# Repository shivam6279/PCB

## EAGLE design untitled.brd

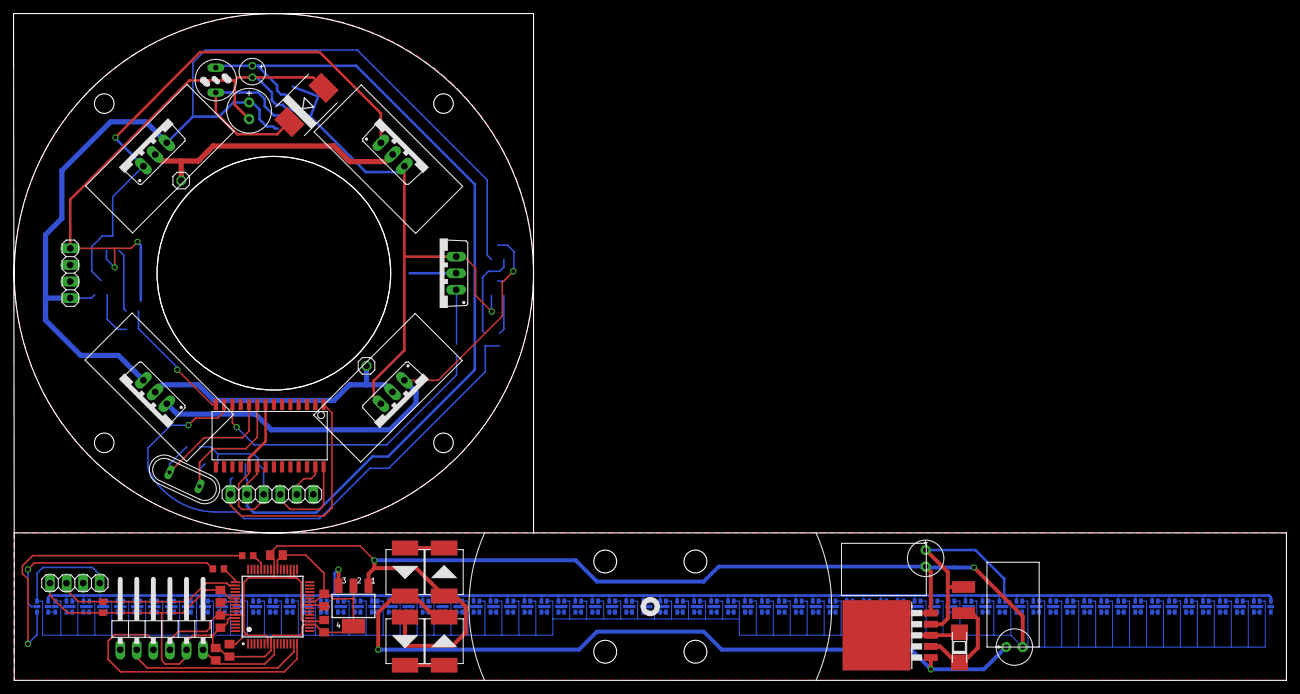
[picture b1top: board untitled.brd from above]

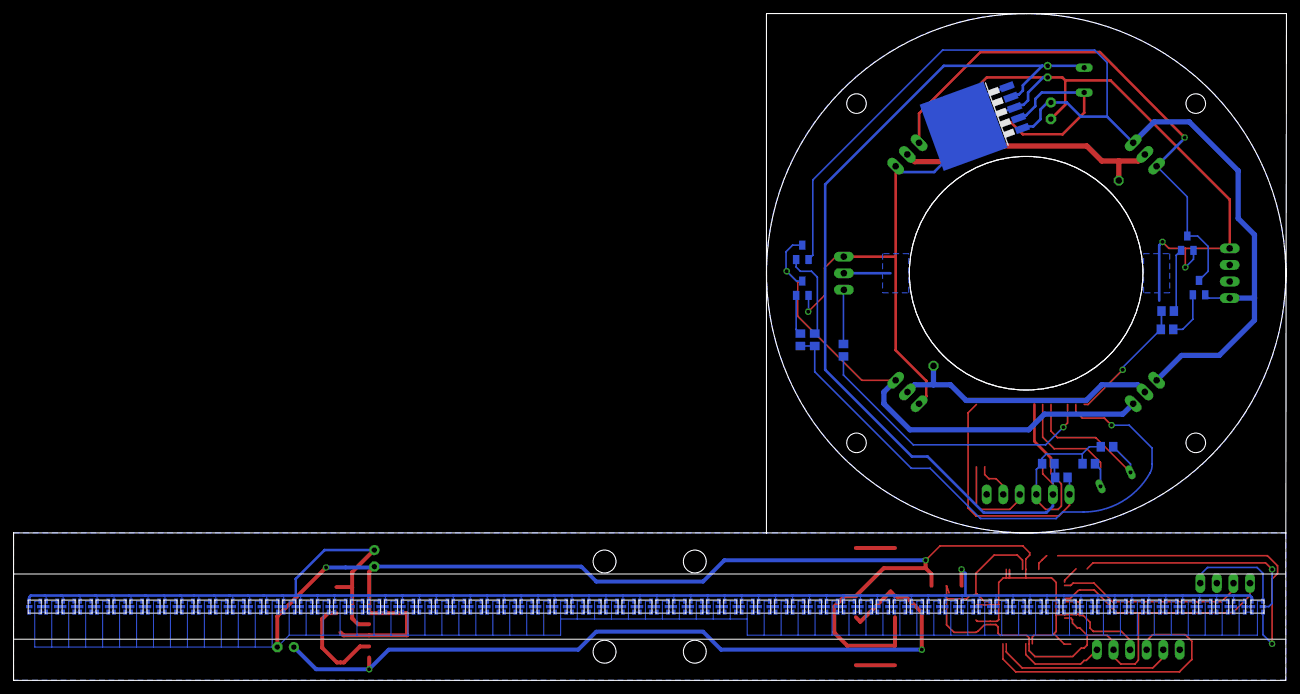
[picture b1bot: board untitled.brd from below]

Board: 2 copper layers, 195.1 x 102.2 mm, 125 parts (87 on the bottom side), 180 nets.

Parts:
C1, C3: E2,5-6E
C2, C4, C5, C6, C7, C8, C9, C10, C11: C0805
C12: E2,5-7
C13: E1,8-4
D1: SOD106A
D2, D3, D4, D5: SMD-DIODE-SCHOTTKY-40V-3A(DO-214AB); DO-214AB
D6: DIODE_SMC
IC1, IC4: LM2576S; TO263-5
IC2: SOT223
IC3: PIC16F876SO; SO28W
JP1: 1X06/90
JP2, JP3: 1X04
JP4: 1X06
JP5, JP6: 1X01
L1: 82114R
L2: L4532P
Q1, Q2, Q3, Q4: SOT23
Q5, Q6: IRF540; TO220BV
Q7, Q9: TO220BV
Q8: QS
R1, R3, R6, R7, R8, R9, R10: R0805
R2, R4, R5: R0603
T2: 2SC1306; TO220BV
U1: PIC32MZ2048EFH064-I/PT; QFP50P1200X1200X120-64N
U$1, U$2, U$3, U$4, U$5, U$6, U$7, U$8, U$9, U$10, U$11, U$12, U$13, U$14, U$15, U$16, U$17, U$18, U$19, U$20, U$21, U$22, U$23, U$24, U$25, U$26, U$27, U$28, U$29, U$30, U$31, U$32, U$33, U$34, U$35, U$36, U$37, U$38, U$39, U$40, U$41, U$42, U$43, U$44, U$45, U$46, U$47, U$48, U$49, U$50, U$51, U$52, U$53, U$54, U$55, U$56, U$57, U$58, U$59, U$60, U$61, U$62, U$63, U$64, U$65, U$66, U$67, U$68, U$69, U$70, U$71, U$72, U$73: 2020LED

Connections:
+3V3: C2.1, C4.1, C5.1, C6.1, C7.1, C8.1, IC2.2, JP1.5, JP2.1, R1.1, R2.1, U1.8, U1.19, U1.26, U1.39, U1.54, U1.60
+5V: C1.+, IC1.4, IC2.3, L2.2, U$1.VCC, U$2.VCC, U$3.VCC, U$4.VCC, U$5.VCC, U$6.VCC, U$7.VCC, U$8.VCC, U$9.VCC, U$10.VCC, U$11.VCC, U$12.VCC, U$13.VCC, U$14.VCC, U$15.VCC, U$16.VCC, U$17.VCC, U$18.VCC, U$19.VCC, U$20.VCC, U$21.VCC, U$22.VCC, U$23.VCC, U$24.VCC, U$25.VCC, U$26.VCC, U$27.VCC, U$28.VCC, U$29.VCC, U$30.VCC, U$31.VCC, U$32.VCC, U$33.VCC, U$34.VCC, U$35.VCC, U$36.VCC, U$37.VCC, U$38.VCC, U$39.VCC, U$40.VCC, U$41.VCC, U$42.VCC, U$43.VCC, U$44.VCC, U$45.VCC, U$46.VCC, U$47.VCC, U$48.VCC, U$49.VCC, U$50.VCC, U$51.VCC, U$52.VCC, U$53.VCC, U$54.VCC, U$55.VCC, U$56.VCC, U$57.VCC, U$58.VCC, U$59.VCC, U$60.VCC, U$61.VCC, U$62.VCC, U$63.VCC, U$64.VCC, U$65.VCC, U$66.VCC, U$67.VCC, U$68.VCC, U$69.VCC, U$70.VCC, U$71.VCC, U$72.VCC, U$73.VCC
+5V1: C9.2, C13.+, IC3.20, IC4.4, JP4.2, L1.2, R9.2
+12V: C12.+, IC4.1, JP3.1, Q3.2, Q4.2, Q7.S, Q9.S
+15V: C3.+, D2.2, D3.2, IC1.1
GND: C1.-, C2.2, C3.-, C4.2, C5.2, C6.2, C7.2, C8.2, D1.A, D4.1, D5.1, IC1.3, IC1.5, IC2.1, JP1.4, JP2.4, U1.7, U1.20, U1.25, U1.34, U1.35, U1.40, U1.55, U1.59, U$1.GND, U$2.GND, U$3.GND, U$4.GND, U$5.GND, U$6.GND, U$7.GND, U$8.GND, U$9.GND, U$10.GND, U$11.GND, U$12.GND, U$13.GND, U$14.GND, U$15.GND, U$16.GND, U$17.GND, U$18.GND, U$19.GND, U$20.GND, U$21.GND, U$22.GND, U$23.GND, U$24.GND, U$25.GND, U$26.GND, U$27.GND, U$28.GND, U$29.GND, U$30.GND, U$31.GND, U$32.GND, U$33.GND, U$34.GND, U$35.GND, U$36.GND, U$37.GND, U$38.GND, U$39.GND, U$40.GND, U$41.GND, U$42.GND, U$43.GND, U$44.GND, U$45.GND, U$46.GND, U$47.GND, U$48.GND, U$49.GND, U$50.GND, U$51.GND, U$52.GND, U$53.GND, U$54.GND, U$55.GND, U$56.GND, U$57.GND, U$58.GND, U$59.GND, U$60.GND, U$61.GND, U$62.GND, U$63.GND, U$64.GND, U$65.GND, U$66.GND, U$67.GND, U$68.GND, U$69.GND, U$70.GND, U$71.GND, U$72.GND, U$73.GND
GND1: C9.1, C10.1, C11.1, C12.-, C13.-, D6.A, IC3.8, IC3.19, IC4.3, IC4.5, JP3.4, JP4.3, Q1.2, Q2.2, Q5.S, Q6.S, T2.3
unnamed: D2.1, D5.2
unnamed: D3.1, D4.2
unnamed: D1.K, IC1.2, L2.1
unnamed: Q1.3, Q3.3, Q5.G, Q7.G
unnamed: JP2.2, R2.2, U1.50
unnamed: U$1.SDI, U$2.SDO
unnamed: U$10.SDO, U$11.SDI
unnamed: U$10.CLKO, U$11.CLKI
unnamed: U$1.CLKI, U$2.CLKO
unnamed: Q2.3, Q4.3, Q6.G, Q9.G
unnamed: U$11.SDO, U$12.SDI
unnamed: JP1.3, U1.16
unnamed: JP1.2, U1.15
unnamed: JP1.6, R1.2, U1.9
unnamed: Q3.1, R6.2
unnamed: R4.2, U$2.SDI
unnamed: U$1.SDO, U$3.SDI
unnamed: R5.2, U$2.CLKI
unnamed: R5.1, U1.49
unnamed: U$1.CLKO, U$3.CLKI
unnamed: R4.1, U1.44
unnamed: Q4.1, R7.2
unnamed: IC3.14, R3.1, R6.1
unnamed: U$11.CLKO, U$12.CLKI
unnamed: U$12.SDO, U$13.SDI
unnamed: IC3.13, R7.1, R8.1
unnamed: U$12.CLKO, U$13.CLKI
unnamed: U$13.SDO, U$14.SDI
unnamed: U$3.SDO, U$4.SDI
unnamed: U$3.CLKO, U$4.CLKI
unnamed: U$13.CLKO, U$14.CLKI
unnamed: U$14.SDO, U$15.SDI
unnamed: U$14.CLKO, U$15.CLKI
unnamed: U$4.SDO, U$5.SDI
unnamed: U$4.CLKO, U$5.CLKI
unnamed: U$15.SDO, U$16.SDI
unnamed: U$15.CLKO, U$16.CLKI
unnamed: U$16.SDO, U$17.SDI
unnamed: U$16.CLKO, U$17.CLKI
unnamed: U$5.SDO, U$6.SDI
unnamed: U$5.CLKO, U$6.CLKI
unnamed: U$17.SDO, U$18.SDI
unnamed: U$17.CLKO, U$18.CLKI
unnamed: U$18.SDO, U$19.SDI
unnamed: U$18.CLKO, U$19.CLKI
unnamed: U$6.SDO, U$7.SDI
unnamed: JP6.1, Q6.D, Q9.D
unnamed: U$19.SDO, U$20.SDI
unnamed: U$19.CLKO, U$20.CLKI
unnamed: JP5.1, Q5.D, Q7.D
unnamed: U$20.SDO, U$21.SDI
unnamed: U$20.CLKO, U$21.CLKI
unnamed: U$21.SDO, U$22.SDI
unnamed: U$6.CLKO, U$7.CLKI
unnamed: U$21.CLKO, U$22.CLKI
unnamed: U$22.SDO, U$23.SDI
unnamed: U$22.CLKO, U$23.CLKI
unnamed: U$23.SDO, U$24.SDI
unnamed: U$23.CLKO, U$24.CLKI
unnamed: U$7.SDO, U$8.SDI
unnamed: U$24.SDO, U$25.SDI
unnamed: U$7.CLKO, U$8.CLKI
unnamed: U$24.CLKO, U$25.CLKI
unnamed: U$25.SDO, U$26.SDI
unnamed: U$25.CLKO, U$26.CLKI
unnamed: U$8.SDO, U$9.SDI
unnamed: U$8.CLKO, U$9.CLKI
unnamed: U$26.SDO, U$27.SDI
unnamed: U$26.CLKO, U$27.CLKI
unnamed: U$9.SDO, U$10.SDI
unnamed: U$9.CLKO, U$10.CLKI
unnamed: U$27.SDO, U$28.SDI
unnamed: U$27.CLKO, U$28.CLKI
unnamed: IC3.1, JP4.1, R9.1
unnamed: U$28.SDO, U$29.SDI
unnamed: U$28.CLKO, U$29.CLKI
unnamed: U$29.SDO, U$30.SDI
unnamed: U$29.CLKO, U$30.CLKI
unnamed: U$30.SDO, U$31.SDI
unnamed: U$30.CLKO, U$31.CLKI
unnamed: U$31.SDO, U$32.SDI
unnamed: U$31.CLKO, U$32.CLKI
unnamed: U$32.SDO, U$33.SDI
unnamed: U$32.CLKO, U$33.CLKI
unnamed: U$33.SDO, U$34.SDI
unnamed: U$33.CLKO, U$34.CLKI
unnamed: U$34.SDO, U$35.SDI
unnamed: U$34.CLKO, U$35.CLKI
unnamed: U$35.SDO, U$36.SDI
unnamed: U$35.CLKO, U$36.CLKI
unnamed: U$36.SDO, U$37.SDI
unnamed: U$36.CLKO, U$37.CLKI
unnamed: U$37.SDO, U$38.SDI
unnamed: U$37.CLKO, U$38.CLKI
unnamed: IC3.28, JP4.4
unnamed: U$38.SDO, U$39.SDI
unnamed: U$38.CLKO, U$39.CLKI
unnamed: U$39.SDO, U$40.SDI
unnamed: U$39.CLKO, U$40.CLKI
unnamed: U$40.SDO, U$41.SDI
unnamed: U$40.CLKO, U$41.CLKI
unnamed: U$41.SDO, U$42.SDI
unnamed: U$41.CLKO, U$42.CLKI
unnamed: U$42.SDO, U$43.SDI
unnamed: U$42.CLKO, U$43.CLKI
unnamed: U$43.SDO, U$44.SDI
unnamed: U$43.CLKO, U$44.CLKI
unnamed: U$44.SDO, U$45.SDI
unnamed: U$44.CLKO, U$45.CLKI
unnamed: U$45.SDO, U$46.SDI
unnamed: U$45.CLKO, U$46.CLKI
unnamed: IC3.27, JP4.5
unnamed: U$46.SDO, U$47.SDI
unnamed: U$46.CLKO, U$47.CLKI
unnamed: U$47.SDO, U$48.SDI
unnamed: U$47.CLKO, U$48.CLKI
unnamed: U$48.SDO, U$49.SDI
unnamed: U$48.CLKO, U$49.CLKI
unnamed: U$49.SDO, U$50.SDI
unnamed: U$49.CLKO, U$50.CLKI
unnamed: U$50.SDO, U$51.SDI
unnamed: U$50.CLKO, U$51.CLKI
unnamed: U$51.SDO, U$52.SDI
unnamed: U$51.CLKO, U$52.CLKI
unnamed: U$52.SDO, U$53.SDI
unnamed: U$52.CLKO, U$53.CLKI
unnamed: U$53.SDO, U$54.SDI
unnamed: U$53.CLKO, U$54.CLKI
unnamed: U$54.SDO, U$55.SDI
unnamed: U$54.CLKO, U$55.CLKI
unnamed: U$55.SDO, U$56.SDI
unnamed: U$55.CLKO, U$56.CLKI
unnamed: U$56.SDO, U$57.SDI
unnamed: U$56.CLKO, U$57.CLKI
unnamed: U$57.SDO, U$58.SDI
unnamed: U$57.CLKO, U$58.CLKI
unnamed: U$58.SDO, U$59.SDI
unnamed: U$58.CLKO, U$59.CLKI
unnamed: U$59.SDO, U$60.SDI
unnamed: U$59.CLKO, U$60.CLKI
unnamed: U$60.SDO, U$61.SDI
unnamed: U$60.CLKO, U$61.CLKI
unnamed: U$61.SDO, U$62.SDI
unnamed: U$61.CLKO, U$62.CLKI
unnamed: U$62.SDO, U$63.SDI
unnamed: U$62.CLKO, U$63.CLKI
unnamed: U$63.SDO, U$64.SDI
unnamed: U$63.CLKO, U$64.CLKI
unnamed: U$64.SDO, U$65.SDI
unnamed: U$64.CLKO, U$65.CLKI
unnamed: U$65.SDO, U$66.SDI
unnamed: U$65.CLKO, U$66.CLKI
unnamed: U$66.SDO, U$67.SDI
unnamed: U$66.CLKO, U$67.CLKI
unnamed: U$67.SDO, U$68.SDI
unnamed: U$67.CLKO, U$68.CLKI
unnamed: U$68.SDO, U$69.SDI
unnamed: U$68.CLKO, U$69.CLKI
unnamed: U$69.SDO, U$70.SDI
unnamed: U$69.CLKO, U$70.CLKI
unnamed: U$70.SDO, U$71.SDI
unnamed: U$70.CLKO, U$71.CLKI
unnamed: U$71.SDO, U$72.SDI
unnamed: U$71.CLKO, U$72.CLKI
unnamed: U$72.SDO, U$73.SDI
unnamed: U$72.CLKO, U$73.CLKI
unnamed: C10.2, IC3.10, Q8.1
unnamed: C11.2, IC3.9, Q8.2
unnamed: Q1.1, R3.2
unnamed: Q2.1, R8.2
unnamed: IC3.12, R10.1
unnamed: R10.2, T2.1
unnamed: D6.C, IC4.2, L1.1
